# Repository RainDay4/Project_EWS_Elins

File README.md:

# Project_EWS_Elins
Project 2019

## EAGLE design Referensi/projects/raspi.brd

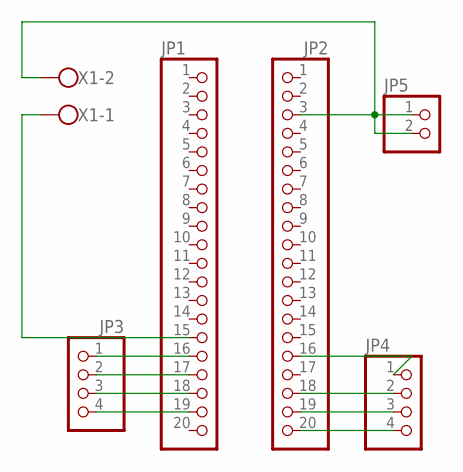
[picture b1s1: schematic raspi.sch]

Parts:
JP1, JP2: PINHD-1X20; 1X20
JP3, JP4: PINHD-1X4; 1X04
JP5: PINHD-1X2; 1X02
X1: W237-102

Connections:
unnamed: JP2.3, JP5.1, JP5.2, X1.2
unnamed: JP2.20, JP4.4
unnamed: JP2.19, JP4.3
unnamed: JP2.18, JP4.2
unnamed: JP2.16, JP4.1
unnamed: JP1.19, JP3.4
unnamed: JP1.18, JP3.3
unnamed: JP1.17, JP3.2
unnamed: JP1.16, JP3.1
unnamed: JP1.15, X1.1

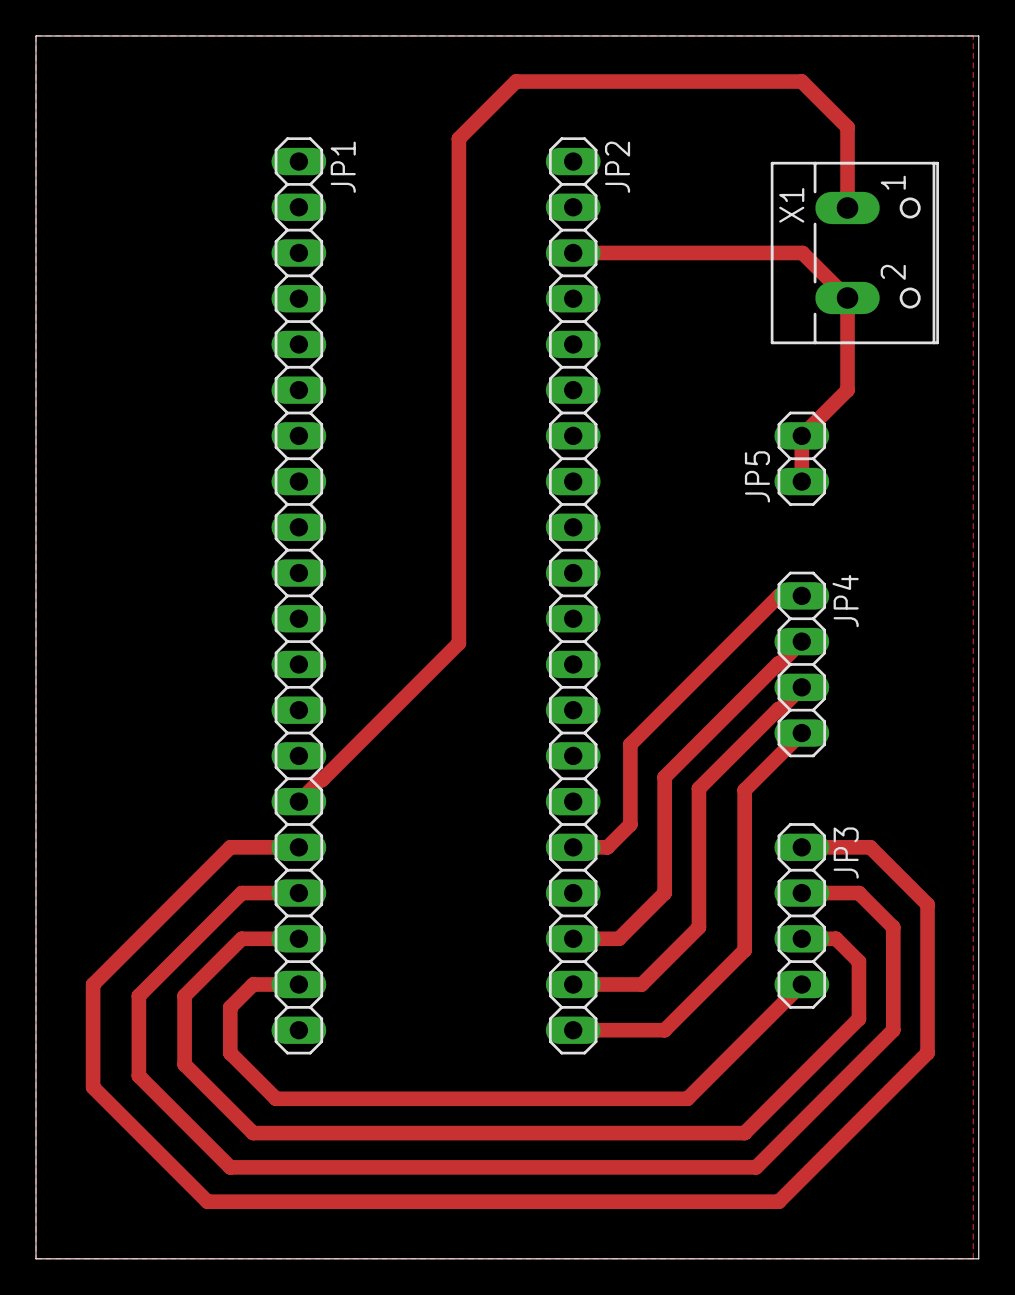
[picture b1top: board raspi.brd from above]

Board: 2 copper layers, 52.4 x 67.9 mm, 6 parts (0 on the bottom side), 10 nets.

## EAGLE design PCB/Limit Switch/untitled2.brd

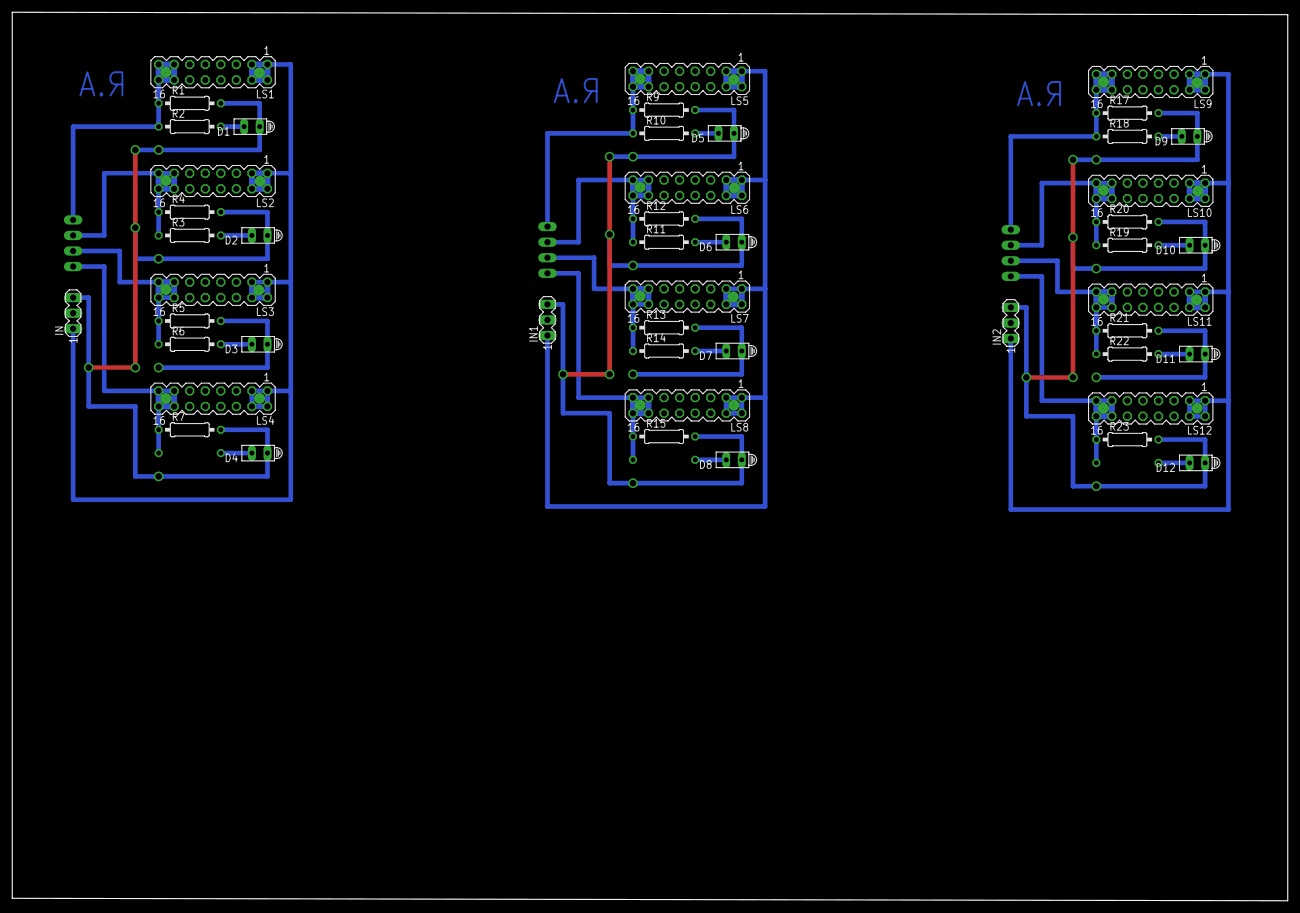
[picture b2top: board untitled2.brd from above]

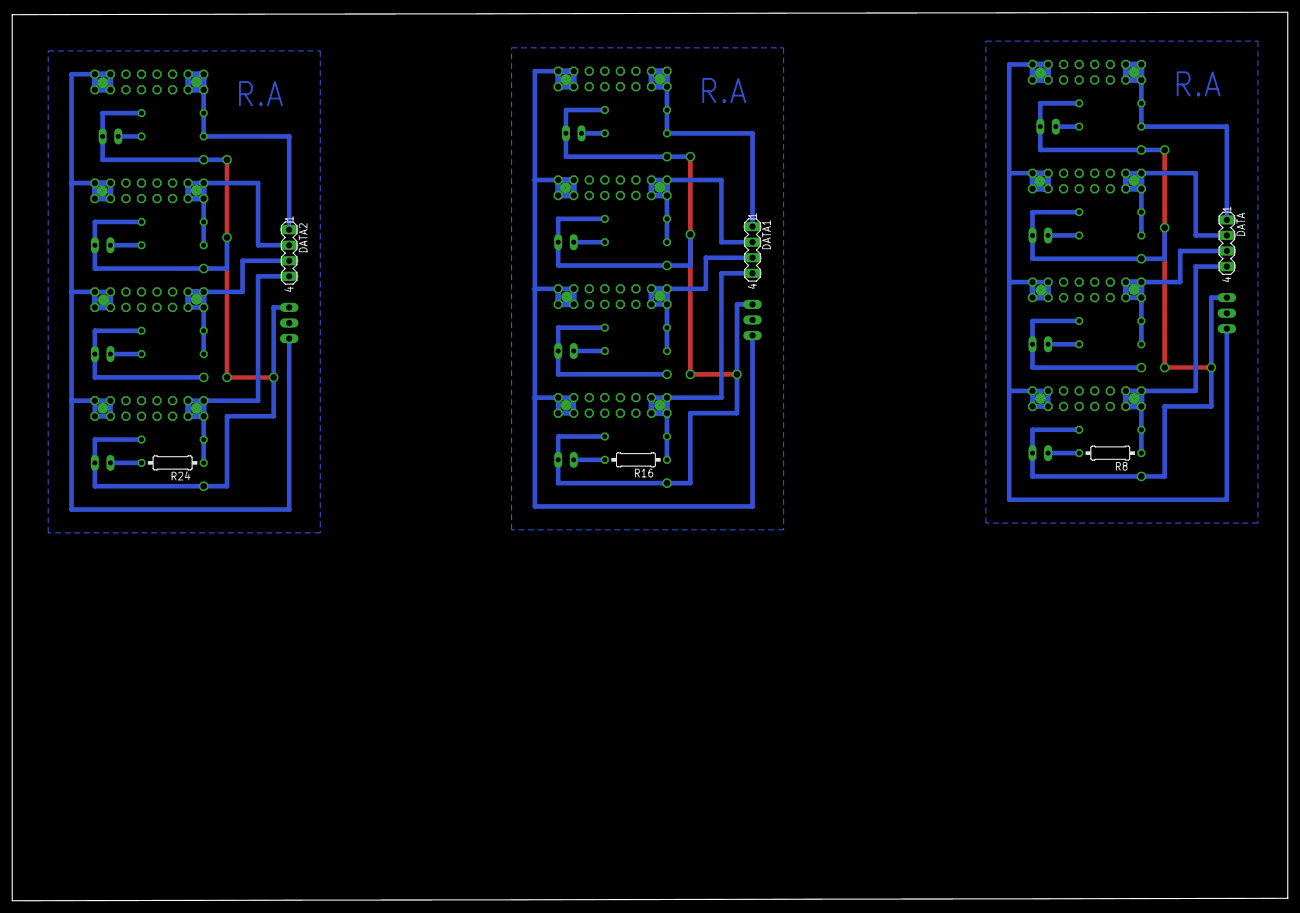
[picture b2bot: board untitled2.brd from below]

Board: 2 copper layers, 208.4 x 145.2 mm, 54 parts (6 on the bottom side), 30 nets.

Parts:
D1, D2, D3, D4, D5, D6, D7, D8, D9, D10, D11, D12: HLMP6
DATA, DATA1, DATA2: MA04-1
IN, IN1, IN2: MA03-1
LS1, LS2, LS3, LS4, LS5, LS6, LS7, LS8, LS9, LS10, LS11, LS12: MA08-2
R1, R2, R3, R4, R5, R6, R7, R8, R9, R10, R11, R12, R13, R14, R15, R16, R17, R18, R19, R20, R21, R22, R23, R24: 0207/10

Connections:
GND: D1.A, D2.A, D3.A, D4.A, IN.3, R1.2, R4.2, R5.2, R7.2
GND1: D5.A, D6.A, D7.A, D8.A, IN1.3, R9.2, R12.2, R13.2, R15.2
GND2: D9.A, D10.A, D11.A, D12.A, IN2.3, R17.2, R20.2, R21.2, R23.2
unnamed: DATA.1, LS1.13, LS1.14, LS1.15, LS1.16, R1.1, R2.1
unnamed: D2.K, R3.2
unnamed: DATA.2, LS2.13, LS2.14, LS2.15, LS2.16, R3.1, R4.1
unnamed: D3.K, R6.2
unnamed: D1.K, R2.2
unnamed: DATA.3, LS3.13, LS3.14, LS3.15, LS3.16, R5.1, R6.1
unnamed: D4.K, R8.2
unnamed: DATA.4, LS4.13, LS4.14, LS4.15, LS4.16, R7.1, R8.1
unnamed: IN.1, LS1.1, LS1.2, LS1.3, LS1.4, LS2.1, LS2.2, LS2.3, LS2.4, LS3.1, LS3.2, LS3.3, LS3.4, LS4.1, LS4.2, LS4.3, LS4.4
unnamed: D5.K, R10.2
unnamed: DATA1.1, LS5.13, LS5.14, LS5.15, LS5.16, R9.1, R10.1
unnamed: D6.K, R11.2
unnamed: DATA1.2, LS6.13, LS6.14, LS6.15, LS6.16, R11.1, R12.1
unnamed: D7.K, R14.2
unnamed: DATA1.3, LS7.13, LS7.14, LS7.15, LS7.16, R13.1, R14.1
unnamed: D8.K, R16.2
unnamed: DATA1.4, LS8.13, LS8.14, LS8.15, LS8.16, R15.1, R16.1
unnamed: IN1.1, LS5.1, LS5.2, LS5.3, LS5.4, LS6.1, LS6.2, LS6.3, LS6.4, LS7.1, LS7.2, LS7.3, LS7.4, LS8.1, LS8.2, LS8.3, LS8.4
unnamed: D9.K, R18.2
unnamed: DATA2.1, LS9.13, LS9.14, LS9.15, LS9.16, R17.1, R18.1
unnamed: D10.K, R19.2
unnamed: DATA2.2, LS10.13, LS10.14, LS10.15, LS10.16, R19.1, R20.1
unnamed: D11.K, R22.2
unnamed: DATA2.3, LS11.13, LS11.14, LS11.15, LS11.16, R21.1, R22.1
unnamed: D12.K, R24.2
unnamed: DATA2.4, LS12.13, LS12.14, LS12.15, LS12.16, R23.1, R24.1
unnamed: IN2.1, LS9.1, LS9.2, LS9.3, LS9.4, LS10.1, LS10.2, LS10.3, LS10.4, LS11.1, LS11.2, LS11.3, LS11.4, LS12.1, LS12.2, LS12.3, LS12.4
